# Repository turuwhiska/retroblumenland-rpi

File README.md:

# retroblumenland

Connect all retro joysticks!!!
2 megadrive joysticks
2 snes joysticks
32 butons for mame/arcade 

added 4 buttons for off, volume, etc.
ir remote receiver for your recicles remotes from old tv for example

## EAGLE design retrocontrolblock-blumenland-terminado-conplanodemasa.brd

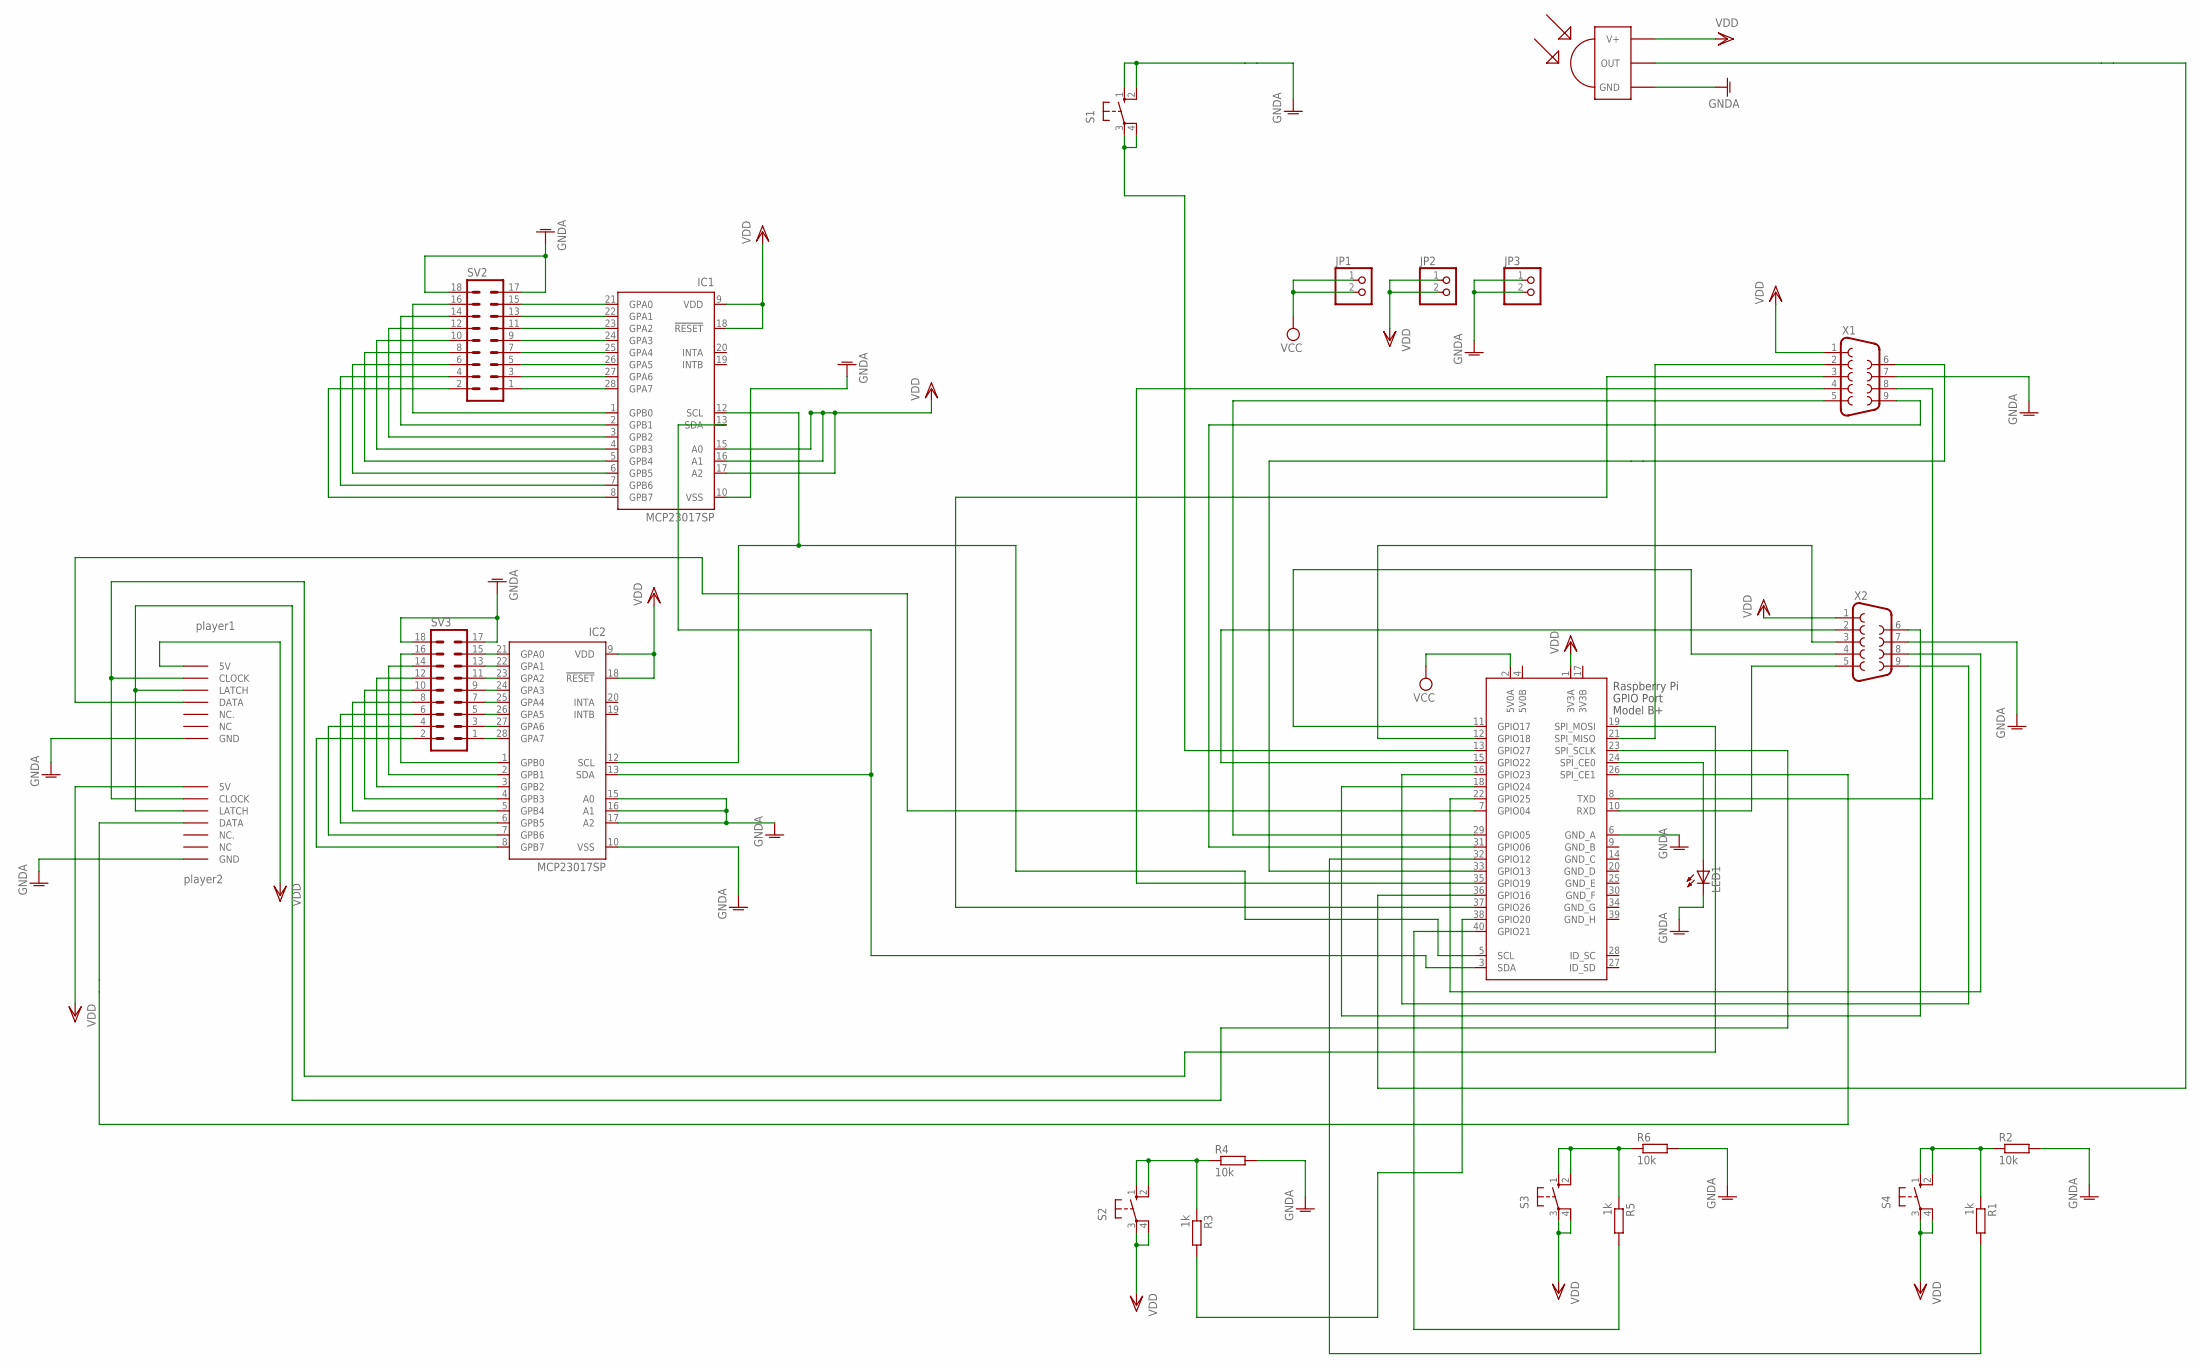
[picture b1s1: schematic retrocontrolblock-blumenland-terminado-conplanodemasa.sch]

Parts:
IC1, IC2: MCP23017SP; DIL28-3
JP1, JP2, JP3: PINHD-1X2; 1X02
LED1: LED5MM
R1, R3, R5: 1k; 0207/7
R2, R4, R6: 10k; 0207/7
S1, S2, S3, S4: 10-XX; B3F-10XX
SV2, SV3: MA09-2
U$1: TSOP4838; TSOP18XX
U$2, U$3: SNESCONN
X1, X2: F09H
X3: RASPI_BOARD_B+#_E0; RASPI_BOARD_B+_EDGES_0DRILL@1

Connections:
3V3B: X3.17 (3V3B)
5V0B: X3.4 (5V0B)
GNDA: IC1.10 (VSS), IC2.10 (VSS), IC2.15 (A0), IC2.16 (A1), IC2.17 (A2), JP3.1, JP3.2, LED1.K (C), R2.2, R4.2, R6.2, S1.1 (S), S1.2 (S1), SV2.17, SV2.18, SV3.17, SV3.18, U$1.GND, U$2.GND, U$3.GND, X1.7, X2.7, X3.6 (GND_A)
GND_B: X3.9 (GND_B)
GND_C: X3.14 (GND_C)
GND_D: X3.20 (GND_D)
GND_E: X3.25 (GND_E)
GND_F: X3.30 (GND_F)
GND_G: X3.34 (GND_G)
GND_H: X3.39 (GND_H)
unnamed: IC2.2 (GPB1), SV3.14
unnamed: LED1.A, X3.24 (SPI_CE0)
unnamed: R3.1, R4.1, S2.1 (S), S2.2 (S1)
unnamed: IC1.21 (GPA0), SV2.15
unnamed: IC1.28 (GPA7), SV2.1
unnamed: IC1.1 (GPB0), SV2.16
unnamed: IC1.8 (GPB7), SV2.2
unnamed: IC2.21 (GPA0), SV3.15
unnamed: IC2.28 (GPA7), SV3.1
unnamed: IC2.1 (GPB0), SV3.16
unnamed: IC2.8 (GPB7), SV3.2
unnamed: IC1.22 (GPA1), SV2.13
unnamed: IC1.23 (GPA2), SV2.11
unnamed: IC1.24 (GPA3), SV2.9
unnamed: IC1.25 (GPA4), SV2.7
unnamed: IC1.26 (GPA5), SV2.5
unnamed: IC1.27 (GPA6), SV2.3
unnamed: IC1.2 (GPB1), SV2.14
unnamed: X2.5, X3.10 (RXD)
unnamed: IC1.3 (GPB2), SV2.12
unnamed: X2.3, X3.12 (GPIO18)
unnamed: IC1.4 (GPB3), SV2.10
unnamed: IC1.5 (GPB4), SV2.8
unnamed: R5.1, R6.1, S3.1 (S), S3.2 (S1)
unnamed: IC1.6 (GPB5), SV2.6
unnamed: IC1.7 (GPB6), SV2.4
unnamed: IC2.7 (GPB6), SV3.4
unnamed: IC2.6 (GPB5), SV3.6
unnamed: IC2.5 (GPB4), SV3.8
unnamed: IC2.4 (GPB3), SV3.10
unnamed: IC2.3 (GPB2), SV3.12
unnamed: X1.5, X3.29 (GPIO05)
unnamed: X1.8, X3.8 (TXD)
unnamed: X1.9, X3.31 (GPIO06)
unnamed: R3.2, X3.38 (GPIO20)
unnamed: X1.6, X3.33 (GPIO13)
unnamed: X1.3, X3.37 (GPIO26)
unnamed: X1.4, X3.35 (GPIO19)
unnamed: X1.2, X3.21 (SPI_MISO)
unnamed: X2.4, X3.11 (GPIO17)
unnamed: S1.3, S1.4 (P1), X3.13 (GPIO27)
unnamed: X2.2, X3.15 (GPIO22)
unnamed: X2.9, X3.16 (GPIO23)
unnamed: X2.6, X3.18 (GPIO24)
unnamed: X2.8, X3.22 (GPIO25)
unnamed: IC2.22 (GPA1), SV3.13
unnamed: IC2.23 (GPA2), SV3.11
unnamed: IC2.24 (GPA3), SV3.9
unnamed: IC2.25 (GPA4), SV3.7
unnamed: IC2.26 (GPA5), SV3.5
unnamed: IC2.27 (GPA6), SV3.3
unnamed: U$1.OUT, X3.36 (GPIO16)
unnamed: U$3.DATA, X3.7 (GPIO04)
unnamed: U$2.CLOCK, U$3.CLOCK, X3.19 (SPI_MOSI)
unnamed: U$2.LATCH, U$3.LATCH, X3.23 (SPI_SCLK)
unnamed: U$2.DATA, X3.26 (SPI_CE1)
unnamed: R5.2, X3.40 (GPIO21)
unnamed: R1.1, R2.1, S4.1 (S), S4.2 (S1)
unnamed: R1.2, X3.32 (GPIO12)
unnamed: IC1.13 (SDA), IC2.13 (SDA), X3.3 (SDA)
unnamed: IC1.12 (SCL), IC2.12 (SCL), X3.5 (SCL)
VCC: JP1.1, JP1.2, X3.2 (5V0A)
VDD: IC1.9 (VDD), IC1.15 (A0), IC1.16 (A1), IC1.17 (A2), IC1.18 (!RESET), IC2.9 (VDD), IC2.18 (!RESET), JP2.1, JP2.2, S2.3, S2.4 (P1), S3.3, S3.4 (P1), S4.3, S4.4 (P1), U$1.VCC (V+), U$2.5V, U$3.5V, X1.1, X2.1, X3.1 (3V3A)

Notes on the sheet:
player1
player2

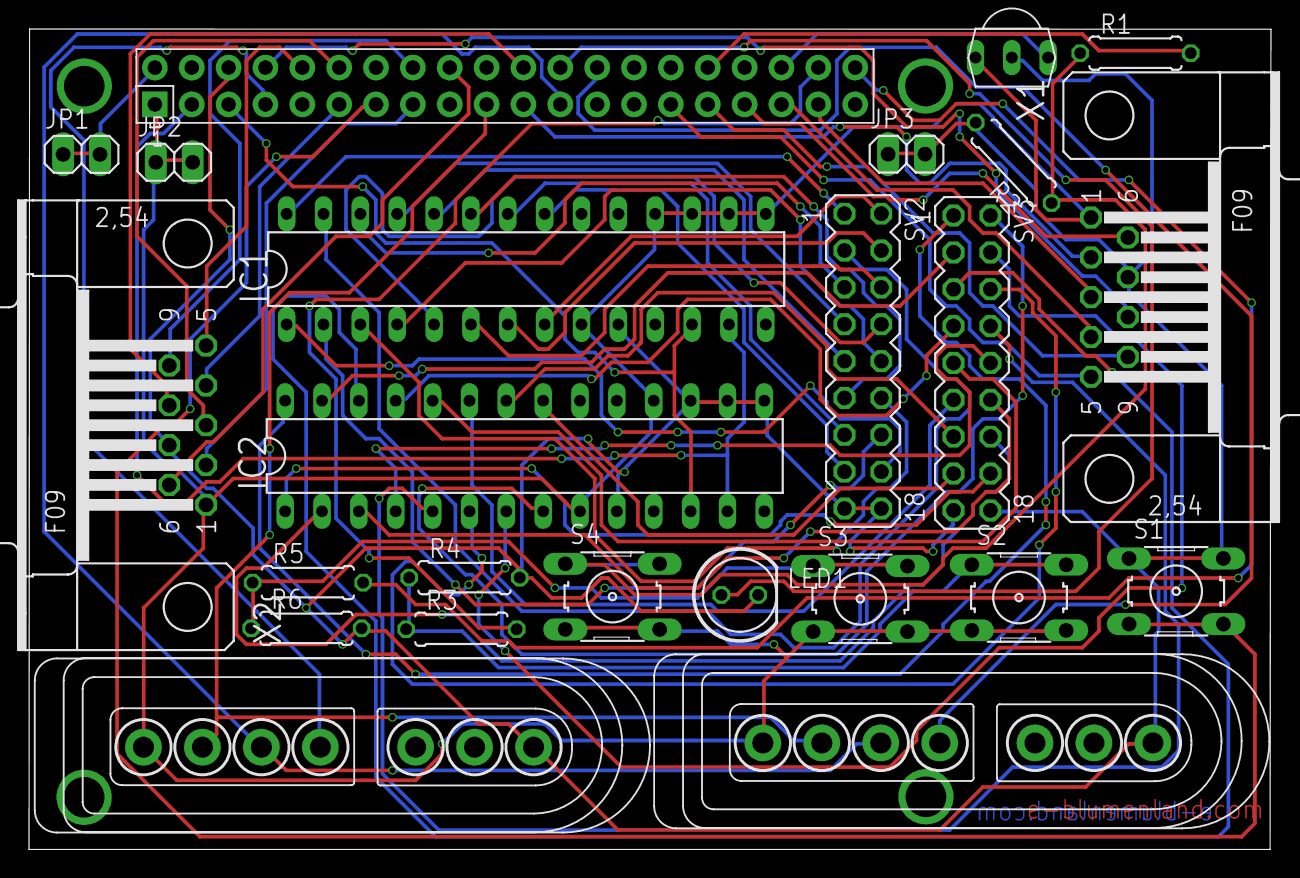
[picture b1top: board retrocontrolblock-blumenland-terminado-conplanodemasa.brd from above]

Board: 2 copper layers, 85.6 x 56.5 mm, 24 parts (0 on the bottom side), 64 nets.

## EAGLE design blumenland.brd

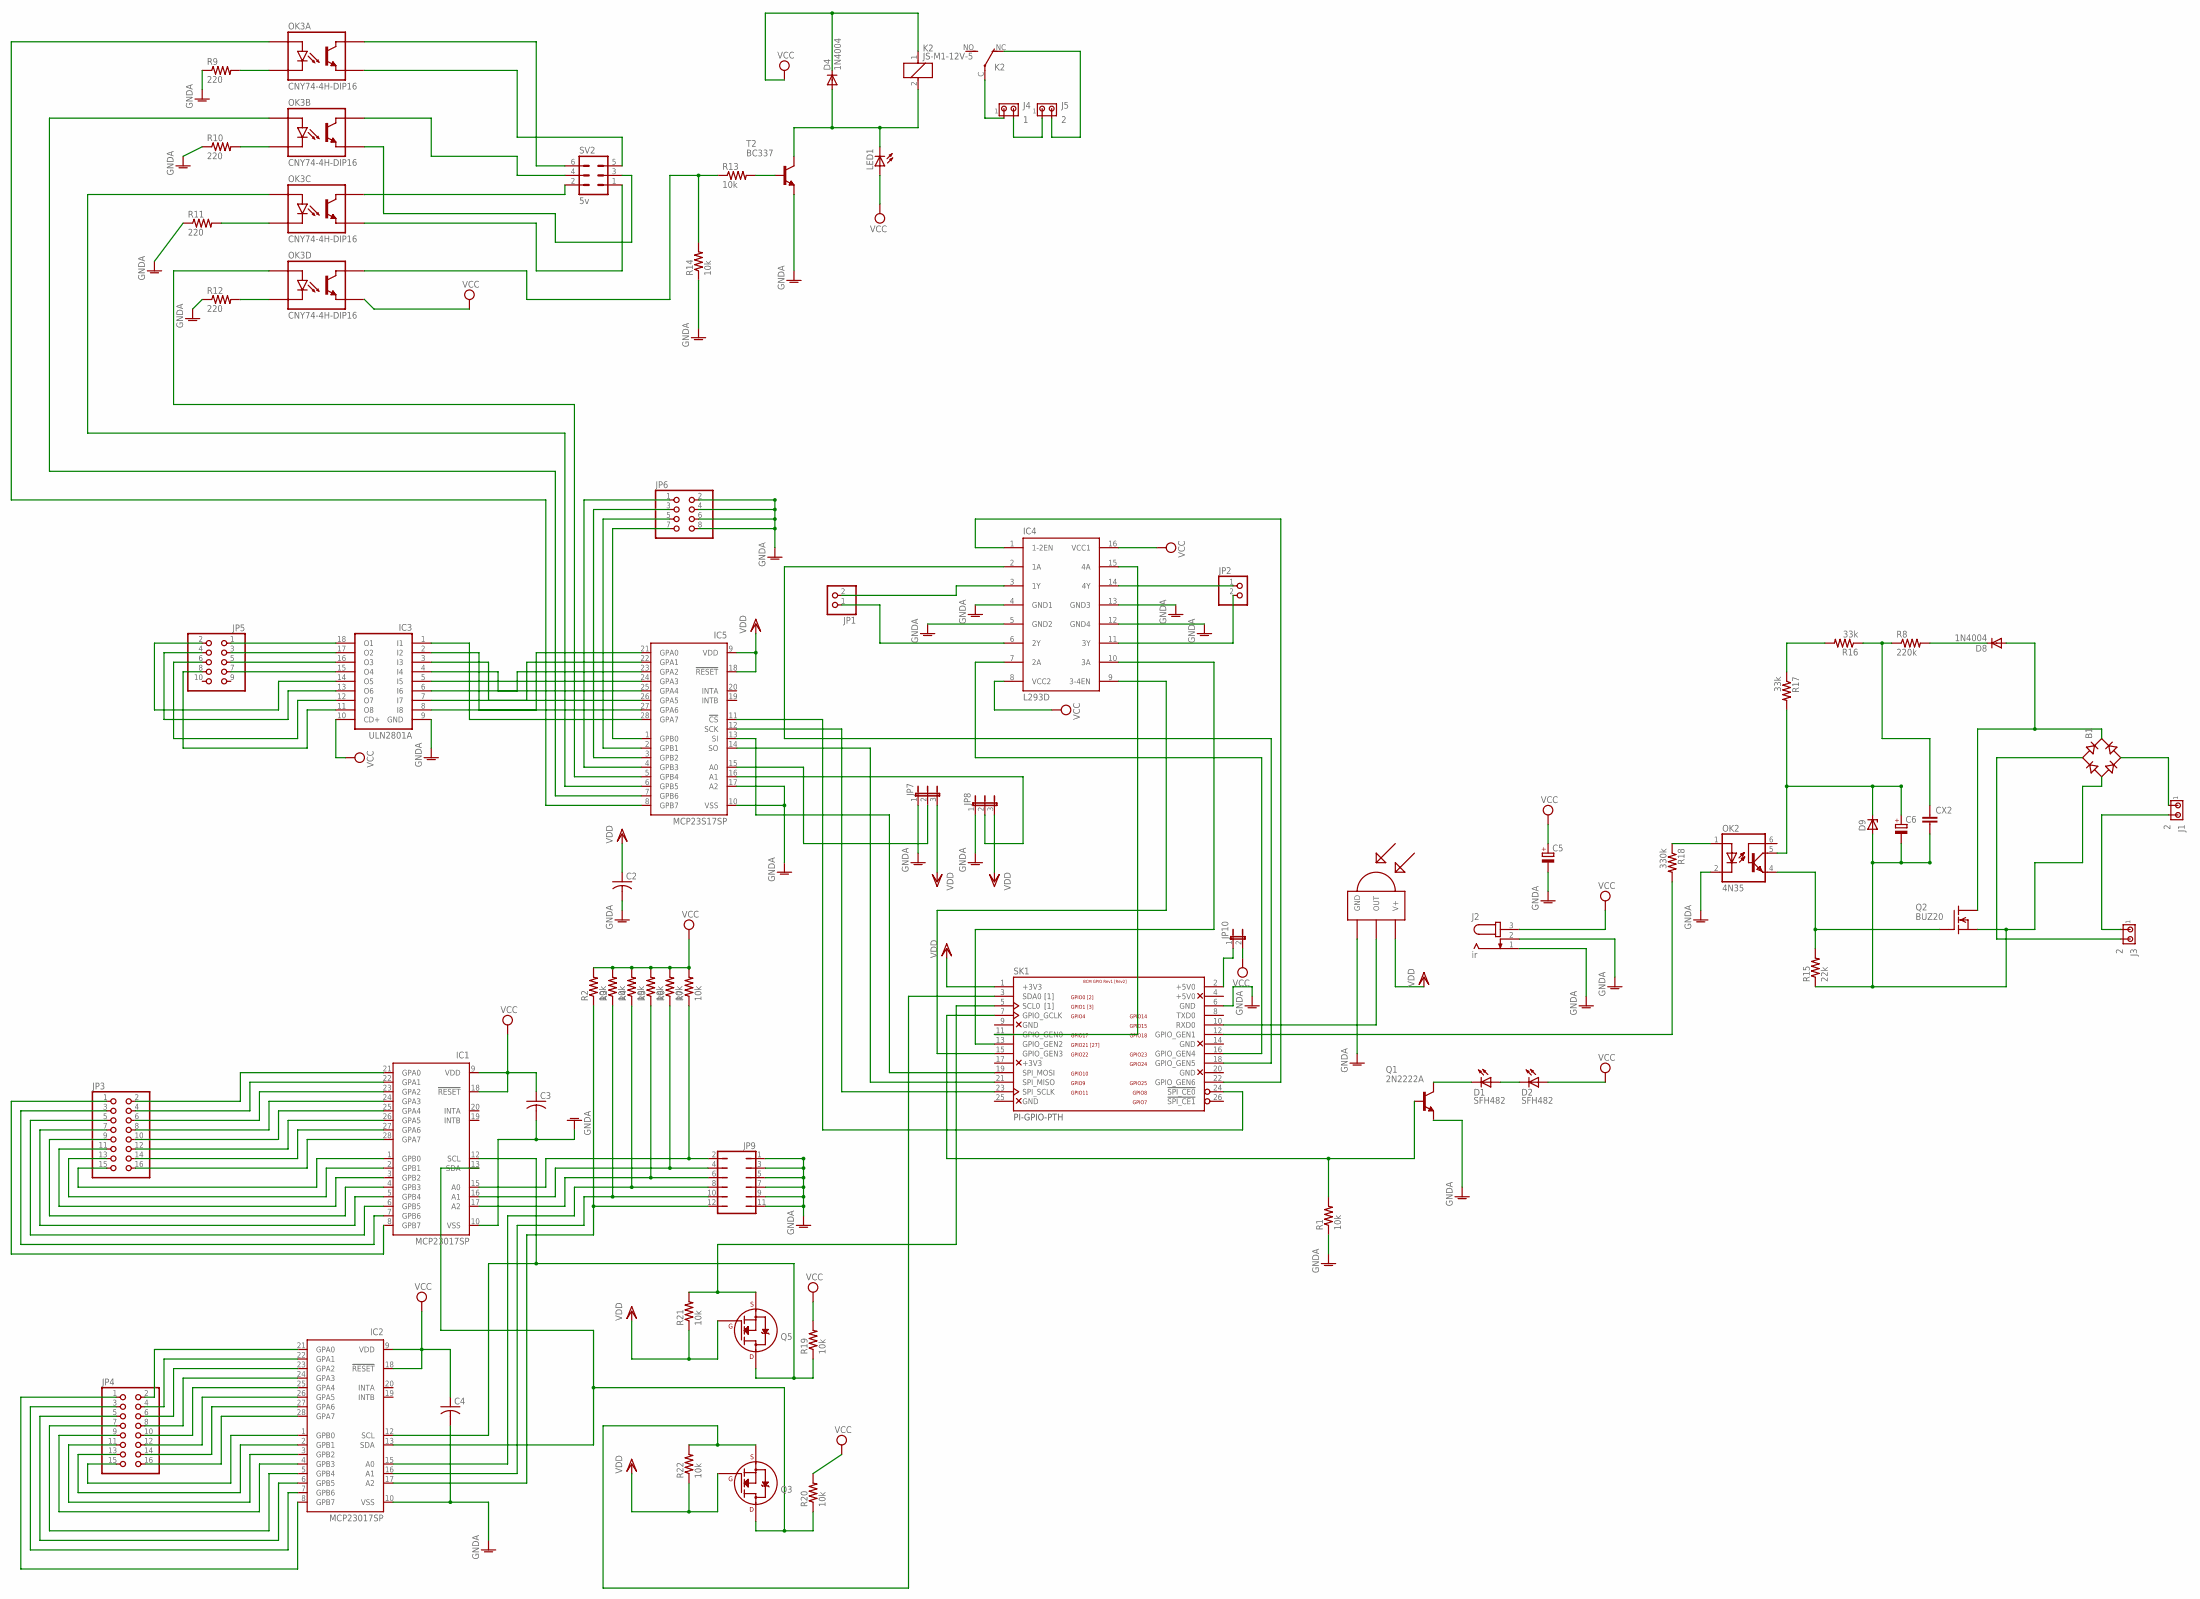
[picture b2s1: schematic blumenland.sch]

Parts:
B1: RB1A
C2, C3, C4: C-US025-025X050; C025-025X050
C5: CPOL-EUE2-5; E2-5
C6: CPOL-EUE2.5-5; E2,5-5
CX2: CXXC10B6; XC10B6
D1, D2: SFH482
D4, D8: 1N4004; DO41-10
D9: ZENER-DIODEDO41Z10; DO41Z10
IC1, IC2: MCP23017SP; DIL28-3
IC3: ULN2801A; DIL18
IC4: L293D; DIL16
IC5: MCP23S17SP; DIL28-3
J1, J3, J5: 2; 1X2MTA
J2: ir; SPC4077
J4: 1; 1X2MTA
JP1, JP2: PINHD-1X2; 1X02
JP3, JP4: PINHD-2X8; 2X08
JP5: PINHD-2X5; 2X05
JP6: PINHD-2X4; 2X04
JP7, JP8: JP2E; JP2
JP9: JP6Q
JP10: JP1E; JP1
K2: JS-M1-12V-5; JS-M
LED1: LED5MM
OK2: 4N35; DIL06
OK3: CNY74-4H-DIP16; DIL16-3
Q1: 2N2222A; TO18
Q2: BUZ20; TO220
Q3, Q5: 2N7000_TO92; TO-92
R1, R2, R3, R4, R5, R6, R7, R19, R20, R21, R22: 10k; 0207/10
R8: 220k; 0207/10
R9, R10, R11, R12: 220; 0204/7
R13, R14: 10k; 0204/7
R15: 22k; 0207/10
R16, R17: 33k; 0207/10
R18: 330k; 0207/10
SK1: PI-GPIO-PTH; GPIO-CONNECTOR
SV2: 5v; MA03-2
T2: BC337; TO92
U$1: TSOP4838; TSOP18XX

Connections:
GNDA: C2.2, C3.2, C4.2, C5.-, IC1.10 (VSS), IC2.10 (VSS), IC3.9 (GND), IC4.4 (GND1), IC4.5 (GND2), IC4.12 (GND4), IC4.13 (GND3), IC5.10 (VSS), IC5.17 (A2), J2.1, J2.2, JP6.2, JP6.4, JP6.6, JP6.8, JP7.1, JP8.1, JP9.1, JP9.3, JP9.5, JP9.7, JP9.9, JP9.11, OK2.2 (C), Q1.1 (E), R1.1, R9.1, R10.1, R11.1, R12.1, R14.1, SK1.6 (GND), T2.1 (E), U$1.GND
unnamed: SK1.10 (RXD0), U$1.OUT
unnamed: D1.A, D2.K (C)
unnamed: D1.K (C), Q1.3 (C)
unnamed: Q1.2 (B), R1.2, SK1.7 (GPIO_GCLK)
unnamed: IC3.1 (I1), IC5.28 (GPA7)
unnamed: IC3.2 (I2), IC5.27 (GPA6)
unnamed: IC3.3 (I3), IC5.26 (GPA5)
unnamed: IC3.4 (I4), IC5.25 (GPA4)
unnamed: IC5.8 (GPB7), OK3.1 (A1)
unnamed: IC5.7 (GPB6), OK3.4 (A1)
unnamed: IC5.6 (GPB5), OK3.5 (A1)
unnamed: IC5.5 (GPB4), OK3.8 (A1)
unnamed: IC5.1 (GPB0), JP6.7
unnamed: IC5.2 (GPB1), JP6.5
unnamed: IC5.3 (GPB2), JP6.3
unnamed: IC5.4 (GPB3), JP6.1
unnamed: IC2.17 (A2), JP9.12, R2.1
unnamed: IC5.15 (A0), JP7.2
unnamed: IC5.16 (A1), JP8.2
unnamed: IC1.15 (A0), JP9.2, R7.1
unnamed: IC4.1 (1-2EN), SK1.22 (GPIO_GEN6)
unnamed: IC1.16 (A1), JP9.4, R6.1
unnamed: IC3.5 (I5), IC5.24 (GPA3)
unnamed: IC4.2 (1A), SK1.18 (GPIO_GEN5)
unnamed: IC1.17 (A2), JP9.6, R5.1
unnamed: IC4.3 (1Y), JP1.2
unnamed: IC4.6 (2Y), JP1.1
unnamed: IC4.14 (4Y), JP2.1
unnamed: IC4.11 (3Y), JP2.2
unnamed: IC4.7 (2A), SK1.16 (GPIO_GEN4)
unnamed: IC3.6 (I6), IC5.23 (GPA2)
unnamed: IC4.15 (4A), SK1.11 (GPIO_GEN0)
unnamed: IC2.2 (GPB1), JP4.13
unnamed: IC1.22 (GPA1), JP3.4
unnamed: IC4.10 (3A), SK1.13 (GPIO_GEN2)
unnamed: IC4.9 (3-4EN), SK1.15 (GPIO_GEN3)
unnamed: IC3.7 (I7), IC5.22 (GPA1)
unnamed: IC3.8 (I8), IC5.21 (GPA0)
unnamed: IC1.21 (GPA0), JP3.2
unnamed: IC2.15 (A0), JP9.8, R4.1
unnamed: IC1.23 (GPA2), JP3.6
unnamed: IC1.24 (GPA3), JP3.8
unnamed: IC2.16 (A1), JP9.10, R3.1
unnamed: IC1.25 (GPA4), JP3.10
unnamed: IC1.26 (GPA5), JP3.12
unnamed: IC1.27 (GPA6), JP3.14
unnamed: IC1.28 (GPA7), JP3.16
unnamed: IC1.2 (GPB1), JP3.13
unnamed: IC1.1 (GPB0), JP3.15
unnamed: IC1.3 (GPB2), JP3.11
unnamed: IC1.4 (GPB3), JP3.9
unnamed: IC1.5 (GPB4), JP3.7
unnamed: IC1.6 (GPB5), JP3.5
unnamed: IC1.7 (GPB6), JP3.3
unnamed: IC1.8 (GPB7), JP3.1
unnamed: IC2.21 (GPA0), JP4.2
unnamed: IC2.22 (GPA1), JP4.4
unnamed: IC2.23 (GPA2), JP4.6
unnamed: IC2.24 (GPA3), JP4.8
unnamed: IC2.25 (GPA4), JP4.10
unnamed: IC2.26 (GPA5), JP4.12
unnamed: IC2.27 (GPA6), JP4.14
unnamed: IC2.28 (GPA7), JP4.16
unnamed: IC2.1 (GPB0), JP4.15
unnamed: IC2.3 (GPB2), JP4.11
unnamed: IC3.18 (O1), JP5.1
unnamed: IC2.4 (GPB3), JP4.9
unnamed: IC2.5 (GPB4), JP4.7
unnamed: IC2.6 (GPB5), JP4.5
unnamed: IC2.7 (GPB6), JP4.3
unnamed: IC2.8 (GPB7), JP4.1
unnamed: IC3.17 (O2), JP5.3
unnamed: IC3.16 (O3), JP5.5
unnamed: IC3.15 (O4), JP5.7
unnamed: IC3.14 (O5), JP5.2
unnamed: IC5.13 (SI), SK1.19 (SPI_MOSI)
unnamed: IC5.14 (SO), SK1.21 (SPI_MISO)
unnamed: IC5.12 (SCK), SK1.23 (SPI_SCLK)
unnamed: IC5.11 (!CS), SK1.24 (!SPI_CE0)
unnamed: IC3.13 (O6), JP5.4
unnamed: IC3.12 (O7), JP5.6
unnamed: IC3.11 (O8), JP5.8
unnamed: OK3.2 (C1), R9.2
unnamed: OK3.6 (C1), R11.2
unnamed: OK3.3 (C1), R10.2
unnamed: OK3.16 (EMITTER1), SV2.5
unnamed: OK3.13 (EMITTER1), SV2.3
unnamed: OK3.12 (EMITTER1), SV2.1
unnamed: OK3.9 (COLLECTOR1), R13.1, R14.2
unnamed: R13.2, T2.2 (B)
unnamed: D4.A, K2.2, LED1.K (C), T2.3 (C)
unnamed: J4.1, K2.C
unnamed: OK3.7 (C1), R12.2
unnamed: J5.2, K2.NC (O)
unnamed: J4.2, J5.1
unnamed: OK3.11 (COLLECTOR1), SV2.2
unnamed: OK3.14 (COLLECTOR1), SV2.4
unnamed: OK3.15 (COLLECTOR1), SV2.6
unnamed: B1.AC1, J3.2
unnamed: B1.AC2, J1.1
unnamed: B1.+, D8.A, Q2.2 (D)
unnamed: R16.2, R17.1
unnamed: CX2.1, R8.1, R16.1
unnamed: OK2.4 (EMI), Q2.1 (G), R15.2
unnamed: D8.C, R8.2
unnamed: C6.+, D9.C, OK2.5 (COL), R17.2
unnamed: R18.2, SK1.12 (GPIO_GEN1)
unnamed: OK2.1 (A), R18.1
unnamed: J1.2, J3.1
unnamed: JP10.1, SK1.2 (+5V0)
unnamed: Q5.1 (S), R21.2, SK1.5 (SCL0)
unnamed: Q3.1 (S), R22.2, SK1.3 (SDA0)
unnamed: B1.-, C6.-, CX2.2, D9.A, Q2.3 (S), R15.1
unnamed: IC1.13 (SDA), IC2.13 (SDA), Q3.3 (D), R20.1
unnamed: IC1.12 (SCL), IC2.12 (SCL), Q5.3 (D), R19.1
VCC: C3.1, C4.1, C5.+, D2.A, D4.C, IC1.9 (VDD), IC1.18 (!RESET), IC2.9 (VDD), IC2.18 (!RESET), IC3.10 (CD+), IC4.8 (VCC2), IC4.16 (VCC1), J2.3, JP10.2, K2.1, LED1.A, OK3.10 (EMITTER1), R2.2, R3.2, R4.2, R5.2, R6.2, R7.2, R19.2, R20.2
VDD: C2.1, IC5.9 (VDD), IC5.18 (!RESET), JP7.3, JP8.3, Q3.2 (G), Q5.2 (G), R21.1, R22.1, SK1.1 (+3V3), U$1.VCC (V+)

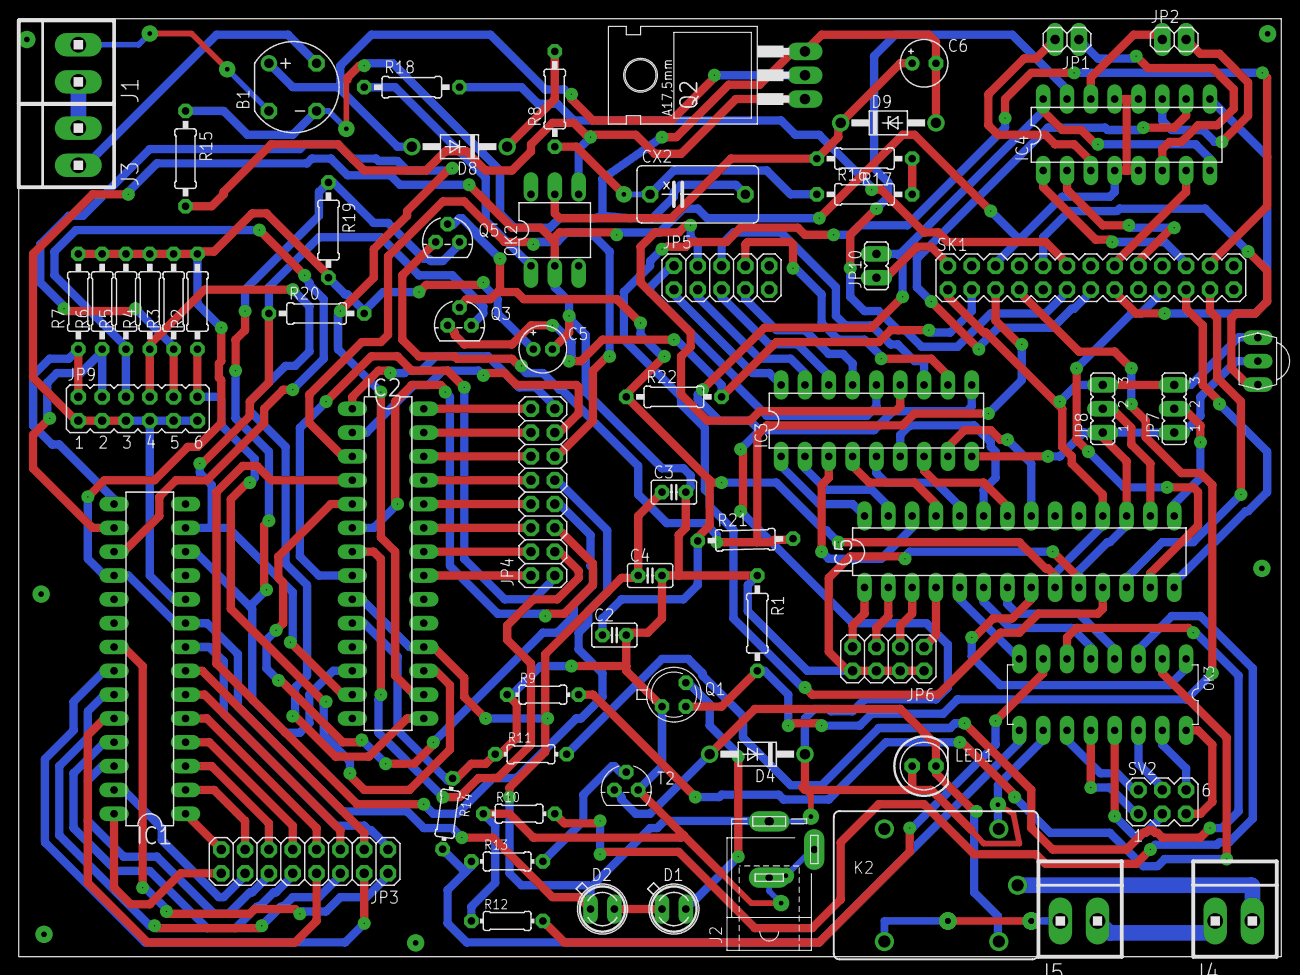
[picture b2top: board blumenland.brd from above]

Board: 2 copper layers, 134.6 x 100.0 mm, 66 parts (0 on the bottom side), 118 nets.

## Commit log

2017-10-09 drivers-blumenland
2017-10-09 blumenland
2017-10-09 elimino archivos innecesarios
2021-11-22 Update controlblockservice
